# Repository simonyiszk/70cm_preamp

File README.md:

Előerősítő 70 cm-es sávra
===========

# Specifikáció
* 435 MHz középfrekcencia
* 23 MHz sávszélesség

# v02 változások
* Új erősítő: PGA-103+
* Új szűrő: SF2446E
* Kapcsrajz szimbólumok külön könyvtárba rendszerezése
* Rajzolatok külön könyvtárba rendszerezése
* cache fájlok hozzáadása .gitignore-hoz
* Bias Tee (tápfeladó)
* "RF" megjelölésű alkatrészek: rezonanciafrekvenciájuk kritikus

# PGA-103+
* Új erősítő: PGA-103+
* Új szűrő: SF2446E

# Megjegyzés
A 'lib-table' fájlok hozzáadják a kapcsrajz szimbólum és rajzolatokat tartalmazó fájlokat a könyvtárak közé.
Amennyiben ez mégsem történik meg, ezt manuálisan kell megtenni.

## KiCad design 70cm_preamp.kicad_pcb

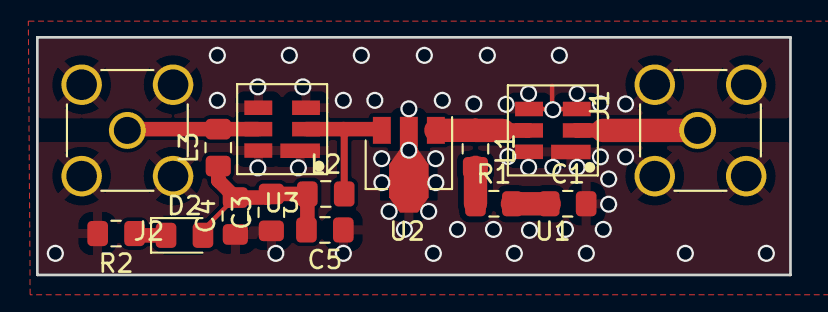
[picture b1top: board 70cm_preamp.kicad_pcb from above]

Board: 2 copper layers, 41.8 x 13.2 mm, 15 parts (0 on the bottom side), 9 nets.

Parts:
C1, C3, C4, C5: 330p; C_0805_2012Metric_Pad1.15x1.40mm_HandSolder
D2: LED; LED_0805_2012Metric_Pad1.15x1.40mm_HandSolder
J1: RF_IN; SMA_Amphenol_901-144_Vertical
J2: RF_OUT; SMA_Amphenol_901-144_Vertical
L1, L2, L3: 620n; L_0805_2012Metric_Pad1.15x1.40mm_HandSolder
R1: 150; R_0805_2012Metric_Pad1.15x1.40mm_HandSolder
R2: 330; R_0805_2012Metric_Pad1.15x1.40mm_HandSolder
U1, U3: SF2446E; SF2446E-Filter_Custom_HandSolder
U2: PGA-103+; SOT-89-3

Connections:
GND: C1.2, C3.1, C4.1, C5.1, J1.2 (Ext), J2.2 (Ext), R2.2, U1.1 (G), U1.3 (G), U1.4 (G), U1.6 (G), U2.2, U3.1 (G), U3.3 (G), U3.4 (G), U3.6 (G)
unnamed: C1.1, R1.2
unnamed: L1.1, U1.5 (RF), U2.1
unnamed: J1.1 (In), U1.2 (RF)
unnamed: C3.2, C4.2, C5.2, D2.2 (A), L2.1, L3.1
unnamed: D2.1 (K), R2.1
unnamed: J2.1 (In), L3.2, U3.5 (RF)
unnamed: L2.2, U2.3, U3.2 (RF)
unnamed: L1.2, R1.1

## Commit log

2019-12-17 Initial commity
2021-01-27 v02.000001
2021-02-03 LM7805 added
2021-02-03 Bias-Tee
2021-02-09 Optikai tuning
2021-02-12 RF alkatreszek
2021-03-09 rajzolatok
2021-03-10 nyák
2021-03-10 PGA-103+
2021-03-11 csak tht sma
2021-03-11 Feliratok
2021-03-12 Change via size
2021-03-12 viák
2021-03-16 Stabilitáshoz RLC
2021-03-16 0805 RLC
2021-03-16 új gerberek
2021-04-05 Dokumentáció
2021-04-12 Zárójelentés
2021-04-12 ADL5523 hivatkozás
2021-04-12 Ellenpárhuzamos, mert Ádi azt mondta
2023-07-06 Add a few parts
2023-07-06 Improve inductor places and resolve throughPCB LED issues
2023-07-10 final checks
2023-07-10 Label corrections
2023-07-11 Fix LED window
2023-07-11 fix gnd
